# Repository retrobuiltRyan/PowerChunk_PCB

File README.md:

# PowerChunk_PCB

https://youtu.be/UuaR92Jk1yQ

Companion Connector PCB for your benchtop power supply.

BoM

| Reference       | Footprint                                                                 | Qty | DigiKey P/N      |
|-----------------|---------------------------------------------------------------------------|-----|------------------|
| J1,J6           | CONN QC TAB 0.250 SOLDER                                                  | 2   | A100452CT-ND     |
| J2,J3           | BATTERY CONTACT 593 SNAP 9V PC PIN                                        | 2   | 36-593-ND        |
| J4              | Barrier_Strip_Thru_Mount_2x1_9.3mm_pitch                                  | 1   | A98481-ND        |
| J5,J7,J8        | TerminalBlock_Phoenix:PT-1,5-4-5.0-H_1x04_P5.00mm_Horizontal              | 3   | 732-10957-ND     |
| J11,J12         | Connector_PinHeader_2.54mm:PinHeader_1x02_P2.54mm_Vertical                | 2   | any              |
| J13,J14         | Connector_BarrelJack:BarrelJack_GCT_DCJ200-10-A_Horizontal                | 2   | EJ508A-ND        |
| R2,R3,R4,R9     | Resistor_SMD:R_1206_3216Metric                                            | 4   | 311-100KFRCT-ND  |
| S1              | SPDT_Rocker_Switch                                                        | 1   | EG5617-ND        |
| U1              | Banana_Jack_Dbl_Turret                                                    | 1   | 501-1316-ND      |

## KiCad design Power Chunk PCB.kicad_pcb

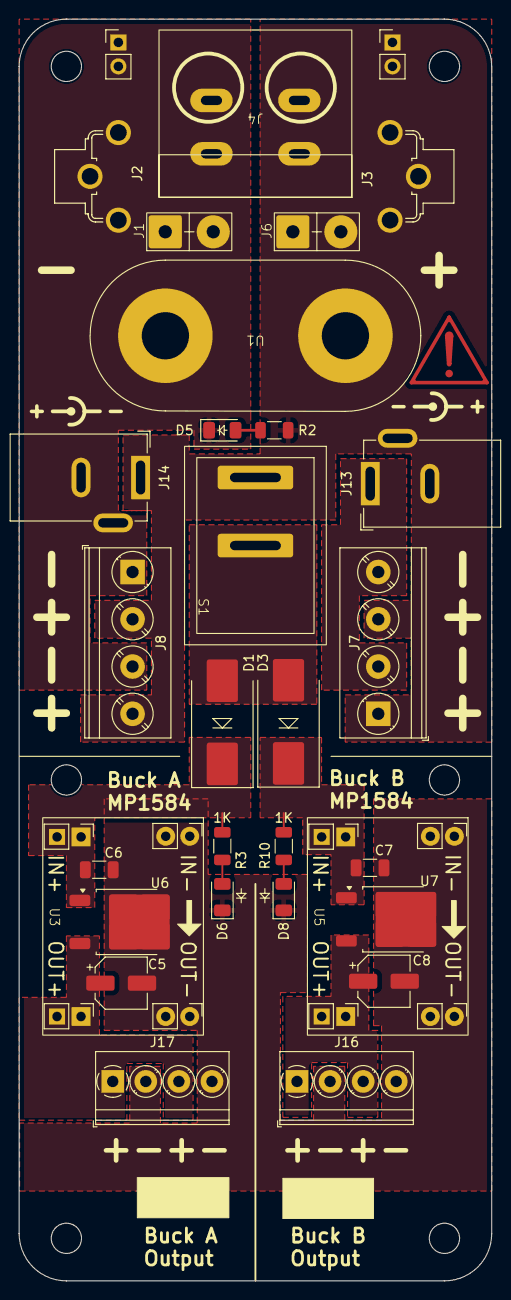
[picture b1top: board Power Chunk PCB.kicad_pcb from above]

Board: 2 copper layers, 50.0 x 133.5 mm, 37 parts (0 on the bottom side), 10 nets.

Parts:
C5, C8: 22uF 50V; CP_Elec_5x5.3
C6, C7: 0.22uF 50V CER; C_1206_3216Metric
D1, D3: D; D_SMC_Handsoldering
D5, D6, D8: LED; LED_1206_3216Metric
H1, H2, H3, H4, H4#2, H4#3: MountingHole; MountingHole_3.2mm_M3
J1, J6: CONN QC TAB 0.250 SOLDER
J2, J3: BATTERY CONTACT 593 SNAP 9V PC PIN
J4: Barrier_Strip_Thru_Mount_2x1_9.3mm_pitch
J7, J8: Screw_Terminal_4_P5.00mm; TerminalBlock_Phoenix_PT-1,5-4-5.0-H_1x04_P5.00mm_Horizontal
J11, J12: PINHD_1x2_Male; PinHeader_1x02_P2.54mm_Vertical
J13, J14: Barrel_Jack; BarrelJack_GCT_DCJ200-10-A_Horizontal
J16, J17: Screw_Terminal_4_P5.00mm; TerminalBlock_Phoenix_PT-1,5-4-3.5-H_1x04_P3.50mm_Horizontal
R2: 5k; R_1206_3216Metric
R3, R10: 1K; R_1206_3216Metric
S1: SPDT_ Rocker_Switch
U1: Banana_Jack_Dbl_Turret
U3, U5: MP1584
U6, U7: L7805; TO-252-2

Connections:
/VCC_A: C6.1, D1.1 (K), R3.1, U3.3 (IN+), U3.4 (IN+), U6.1 (IN)
/VCC_B: C7.1, D3.1 (K), R10.1, U5.3 (IN+), U5.4 (IN+), U7.1 (IN)
/VOUT_A: C5.1, J17.1, J17.3, U3.5 (OUT+), U3.6 (OUT+), U6.3 (OUT)
/VOUT_B: C8.1, J16.1, J16.3, U5.5 (OUT+), U5.6 (OUT+), U7.3 (OUT)
GND: C5.2, C6.2, C7.2, C8.2, D5.1 (K), D6.1 (K), D8.1 (K), J1.1, J1.2, J2.1, J2.2, J2.3, J4.2, J7.2, J7.4, J8.1, J8.3, J11.1, J11.2, J13.1, J14.2, J16.2, J16.4, J17.2, J17.4, U1.2 (V-), U3.1 (IN-), U3.2 (IN-), U3.7 (OUT-), U3.8 (OUT-), U5.1 (IN-), U5.2 (IN-), U5.7 (OUT-), U5.8 (OUT-), U6.2 (GND), U7.2 (GND)
unnamed: D1.2 (A), D3.2 (A), S1.2 (COM)
unnamed: D5.2 (A), R2.2
unnamed: D6.2 (A), R3.2
unnamed: D8.2 (A), R10.2
VDC: J3.1, J3.2, J3.3, J4.1, J6.1, J6.2, J7.1, J7.3, J8.2, J8.4, J12.1, J12.2, J13.2, J14.1, R2.1, S1.1 (IN_A), U1.1 (V+)

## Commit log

2025-05-25 design files
2025-05-25 Update README.md
    bom added
2025-07-13 kiCAD design files
2025-07-13 kiCAD design files (obsolete version)
2025-07-13 3D print file (PCB base)

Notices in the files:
Power Chunk PCB.kicad_pcb:
(c) 2025 Ryan Bates
